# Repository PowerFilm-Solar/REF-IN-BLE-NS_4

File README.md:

# Thank you for your interest in PowerFilm's solar powered BLE reference Designs! Navigate to the Wiki tab to get started: https://github.com/PowerFilm-Solar/REF-IN-BLE-NS_4/wiki

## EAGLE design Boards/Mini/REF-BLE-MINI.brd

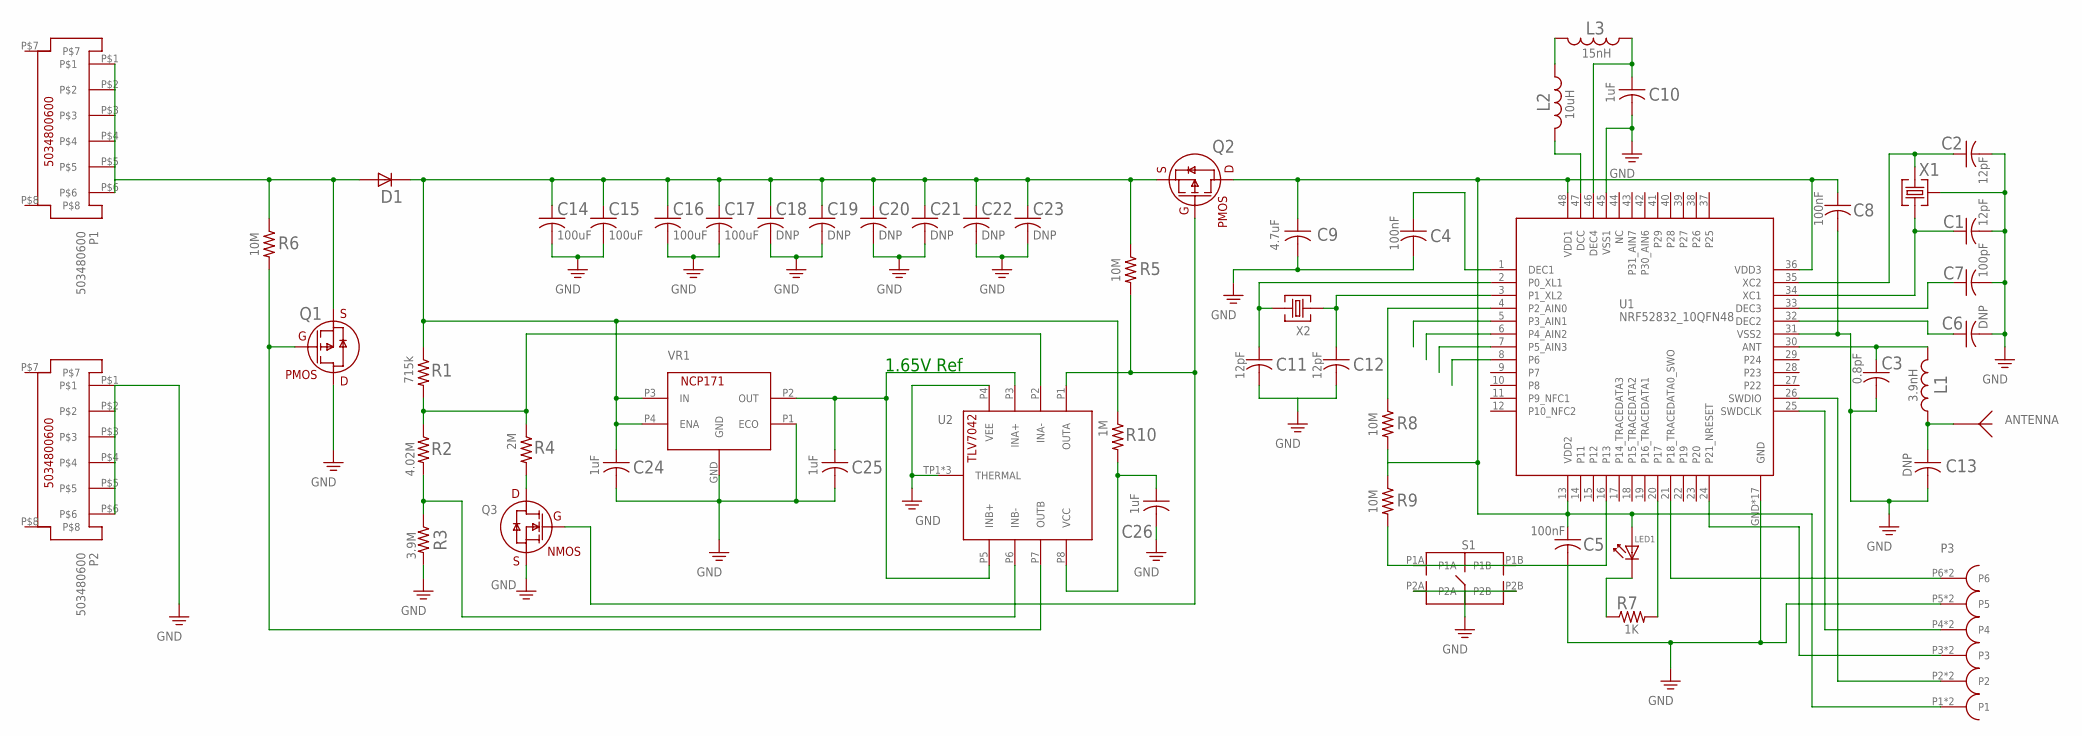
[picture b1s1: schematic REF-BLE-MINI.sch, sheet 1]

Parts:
ANTENNA: BLE-ANTENNA-NORDIC-2
C1, C2, C11, C12: 12pF; C0603
C3: 0.8pF; C0603
C4, C5, C8: 100nF; C0603
C6, C13: DNP; C0603
C7: 100pF; C0603
C9: 4.7uF; C0603
C10, C24, C25, C26: 1uF; C0603
C14, C15, C16, C17: 100uF; C1206
C18, C19, C20, C21, C22, C23: DNP; C1206
D1: BAT43WS-E3-08; SOD-323-VISHAY
L1: 3.9nH; L0603
L2: 10uH; L0603
L3: 15nH; L0603
LED1: LTST-20KGKT; TST-20KGKT
P1, P2: 503480600; 5034800600
P3: EC-06-CTX
Q1, Q2: DMG2305U-13; SOT-23-3-DIODESINC
Q3: NX138AKR; SOT-23-3-RENESAS
R1: 715k; R0603
R2: 4.02M; R0603
R3: 3.9M; R0603
R4: 2M; R0603
R5, R6, R8, R9: 10M; R0603
R7: 1K; R0603
R10: 1M; R0603
S1: EVQ-P7A01P
U1: NRF52832_10QFN48; NRF52832_10
U2: TLV7042DSG
VR1: NCP171
X1: FA-128-32MHZMF10Z-AJ5; FA-128-EPSON
X2: FC-135-32.7680KA-AC0

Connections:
GND: C1.2, C2.2, C3.2, C4.2, C5.2, C6.2, C7.2, C8.2, C9.2, C10.2, C11.2, C12.2, C13.2, C14.2, C15.2, C16.2, C17.2, C18.2, C19.2, C20.2, C21.2, C22.2, C23.2, C24.2, C25.2, P2.P$1, P2.P$2, P2.P$3, P2.P$4, P2.P$5, P2.P$6, P3.P5, P3.P11 (P5), Q1.3 (D), Q3.2 (S), R3.2, S1.P2A, S1.P2B, U1.31 (VSS2), U1.45 (VSS1), U1.GND, U1.P$2 (GND), U1.P$3 (GND), U1.P$4 (GND), U1.P$5 (GND), U1.P$6 (GND), U1.P$7 (GND), U1.P$8 (GND), U1.P$9 (GND), U1.P$10 (GND), U1.P$11 (GND), U1.P$12 (GND), U1.P$13 (GND), U1.P$14 (GND), U1.P$15 (GND), U1.P$16 (GND), U1.P$17 (GND), U2.P4 (VEE), U2.TP1 (THERMAL), U2.TP2 (THERMAL), U2.TP3 (THERMAL), VR1.GND, VR1.P1 (ECO), X1.P2 (P3), X1.P4 (P3)
unnamed: L2.2, U1.47 (DCC)
unnamed: L2.1, L3.2
unnamed: C10.1, L3.1, U1.46 (DEC4)
unnamed: C12.1, U1.3 (P1_XL2), X2.P$1 (1)
unnamed: C4.1, U1.1 (DEC1)
unnamed: C2.1, U1.35 (XC2), X1.P1 (2)
unnamed: C1.1, U1.34 (XC1), X1.P3 (1)
unnamed: C3.1, L1.2, U1.30 (ANT)
unnamed: ANTENNA.P$1, ANTENNA.P$2, C13.1, L1.1
unnamed: C7.1, U1.33 (DEC3)
unnamed: C6.1, U1.32 (DEC2)
unnamed: D1.P2, P1.P$1, P1.P$2, P1.P$3, P1.P$4, P1.P$5, P1.P$6, Q1.2 (S), R6.1
unnamed: C11.1, U1.2 (P0_XL1), X2.P$2 (2)
unnamed: C14.1, C15.1, C16.1, C17.1, C18.1, C19.1, C20.1, C21.1, C22.1, C23.1, C24.1, D1.P1, Q2.2 (S), R1.1, R5.1, R10.1, VR1.P3 (IN), VR1.P4 (ENA)
unnamed: R1.2, R2.1, R4.1, U2.P2 (INA-)
unnamed: Q2.1 (G), Q3.1 (G), R5.2, U2.P1 (OUTA)
unnamed: LED1.C, R7.1
unnamed: R2.2, R3.1, U2.P6 (INB-)
unnamed: R7.2, U1.20 (P17)
unnamed: C25.1, U2.P3 (INA+), U2.P5 (INB+), VR1.P2 (OUT)
unnamed: P3.P4, P3.P10 (P4), U1.25 (SWDCLK)
unnamed: P3.P3, P3.P9 (P3), U1.24 (P21_NRESET)
unnamed: Q1.1 (G), R6.2, U2.P7 (OUTB)
unnamed: R9.2, S1.P1A, S1.P1B, U1.16 (P13)
unnamed: P3.P6, P3.P12 (P6), U1.21 (P18_TRACEDATA0_SWO)
unnamed: P3.P2, P3.P8 (P2), U1.26 (SWDIO)
unnamed: R8.1, U1.4 (P2_AIN0)
unnamed: C5.1, C8.1, C9.1, LED1.A, P3.P1, P3.P7 (P1), Q2.3 (D), R8.2, R9.1, U1.13 (VDD2), U1.36 (VDD3), U1.48 (VDD1)
unnamed: Q3.3 (D), R4.2
unnamed: C26.1, R10.2, U2.P8 (VCC)
PE: C26.2

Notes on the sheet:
1.65V Ref

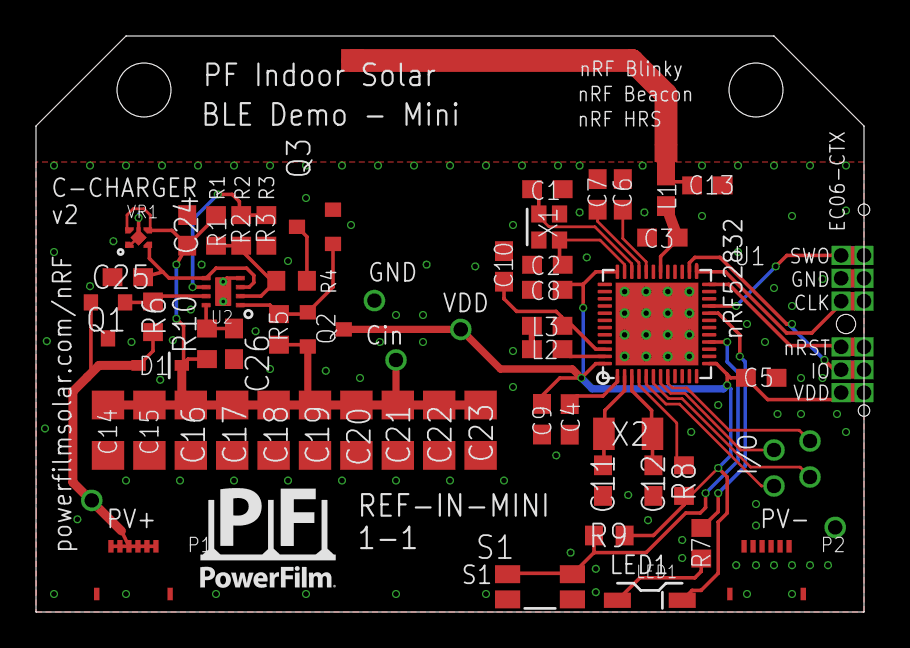
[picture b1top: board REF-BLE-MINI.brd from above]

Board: 2 copper layers, 46.0 x 32.0 mm, 54 parts (0 on the bottom side), 31 nets.

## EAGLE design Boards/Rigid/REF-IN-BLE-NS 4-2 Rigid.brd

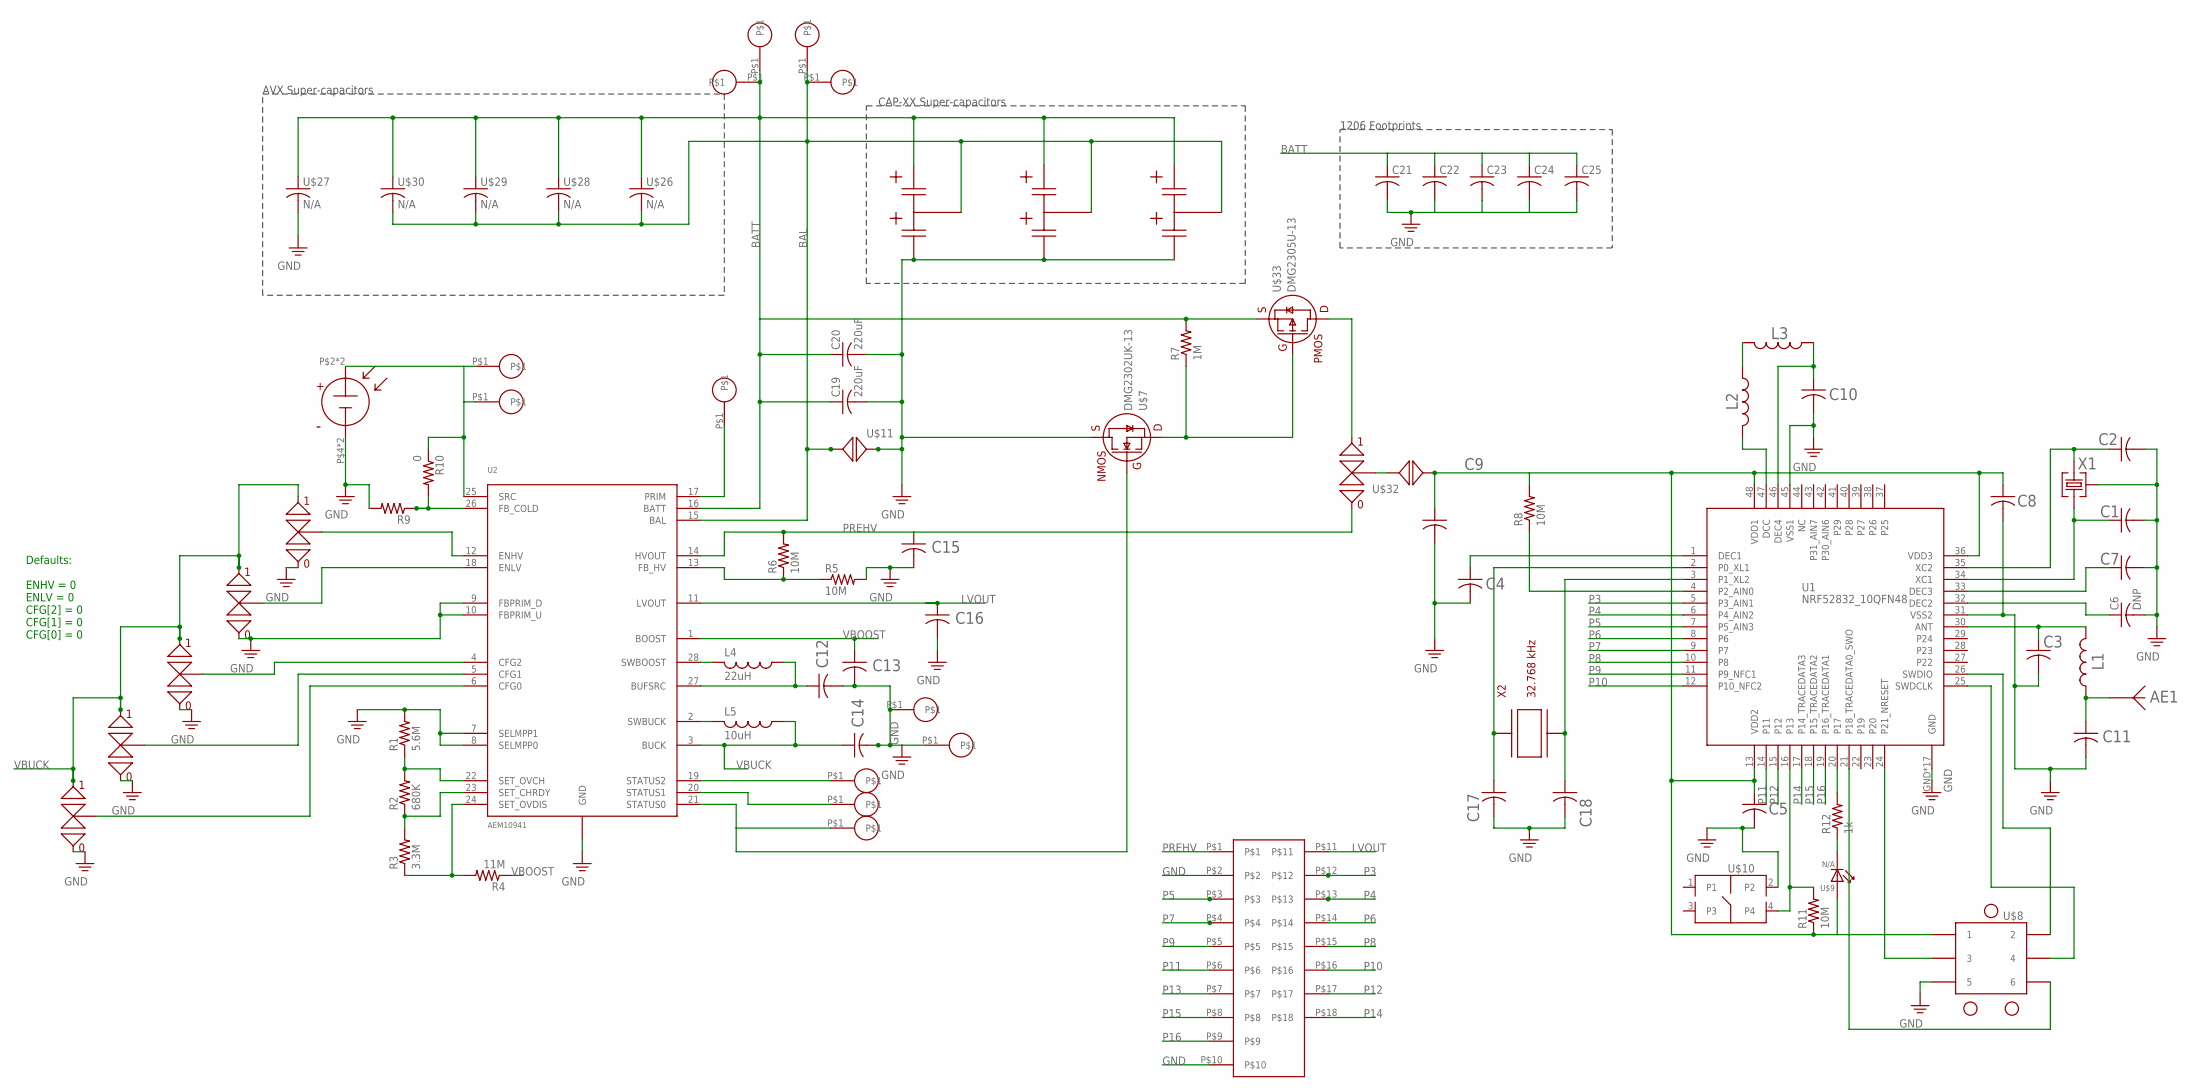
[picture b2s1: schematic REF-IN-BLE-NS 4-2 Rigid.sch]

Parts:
AE1: 2.4GHZ_ANTENNAFLIPPED; BLE_ANTENNA_NORDIC_FLIPPED
C1, C2: 12pF; C0603
C3: 0.8pF; C0603
C4, C5, C8: 100nF; C0603
C6, C11: DNP; C0603
C7: 100pF; C0603
C9: 4.7uF; C0603
C10: 1uF; C0603
C12, C14, C15, C16: 10uF; C0603
C13: 22uF; C0603
C17, C18: 12p; C0603
C19, C20: 220uF; C1206
C21, C22, C23, C24, C25: C-USC1206; C1206
L1: 3.9nH; L0603
L2, L5: 10uH; L0603
L3: 15nH; L0603
L4: 22uH; L1206
R1: 5.6M; R0603
R2: 680K; R0603
R3: 3.3M; R0603
R4: 11M; R0603
R5, R6, R8, R11: 10M; R0603
R7: 1M; R0603
R9: R-US_R0603; R0603
R10: 0; R0603
R12: 1k; R0603
U1: NRF52832_10QFN48; NRF52832_10
U2: AEM10941; QFN28_5X5_05PITCH
U$2, U$3, U$4, U$5, U$6: N/A; DOUBLE_SOLDER_BRIDGE_0_CLOSED
U$7: DMG2302UK-13; SOT-23-3-DIODESINC
U$8: N/A; TC2030-IDC
U$9: N/A; APT1608LZGCK
U$10: MJTP1140; MJTP1140A
U$11, U$32: SOLDER_BRIGDECLOSED; SOLDER_BRIDGE_CLOSED
U$12, U$13, U$14, U$15, U$17, U$18, U$19, U$35, U$36, U$39, U$40, U$41: N/A; 1MM_PAD
U$16: SOLAR_CELL_LL200-2.4-37; SOLAR_CELL_37X54MM
U$20: 18PIN_CONN; 20PIN_CONN
U$23: N/A; CAP-XX_A-TYPE
U$24: N/A; CAP-XX_S-TYPE
U$25: N/A; CAP-XX_W-TYPE
U$26: N/A; BZ01_L-TYPE
U$27: N/A; BZ059_N-TYPE
U$28: N/A; BZ01_S-TYPE
U$29: N/A; BZ05_S-TYPE
U$30: N/A; BZ09_S-TYPE
U$31: DOUBLE_SOLDER_BRIDGE1_CLOSED; DOUBLE_SOLDER_BRIDGE_1_CLOSED
U$33: DMG2305U-13; SOT-23-3-DIODESINC
X1: 32 MHz; FA-128-EPSON
X2: 32.768 kHz; FC-135

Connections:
BAL: U2.15 (BAL), U$11.P$1 (P1), U$19.P$1, U$23.P$1 (BAL), U$24.P$1 (BAL), U$25.P$1 (BAL), U$26.P$3 (2), U$26.P$4 (2), U$28.P$3 (2), U$29.P$3 (2), U$30.P$3 (2), U$41.P$1
BATT: C19.1, C20.1, C21.1, C22.1, C23.1, C24.1, C25.1, R7.2, U2.16 (BATT), U$18.P$1, U$23.P$2 (+), U$24.P$2 (+), U$25.P$2 (+), U$26.P$1 (1), U$26.P$2 (1), U$27.P$1 (1), U$28.P$1 (1), U$28.P$2 (1), U$29.P$1 (1), U$29.P$2 (1), U$30.P$1 (1), U$30.P$2 (1), U$33.2 (S), U$40.P$1
GND: C1.2, C2.2, C3.2, C4.2, C5.2, C6.2, C7.2, C8.2, C9.2, C10.2, C11.2, C12.2, C13.2, C14.2, C15.2, C16.2, C17.2, C18.2, C19.2, C20.2, C21.2, C22.2, C23.2, C24.2, C25.2, R1.2, R5.2, R9.2, U1.31 (VSS2), U1.45 (VSS1), U1.GND, U1.P$2 (GND), U1.P$3 (GND), U1.P$4 (GND), U1.P$5 (GND), U1.P$6 (GND), U1.P$7 (GND), U1.P$8 (GND), U1.P$9 (GND), U1.P$10 (GND), U1.P$11 (GND), U1.P$12 (GND), U1.P$13 (GND), U1.P$14 (GND), U1.P$15 (GND), U1.P$16 (GND), U1.P$17 (GND), U2.7 (SELMPP1), U2.8 (SELMPP0), U2.9 (FBPRIM_D), U2.10 (FBPRIM_U), U2.GND, U2.GND1 (GND), U2.GND2 (GND), U2.GND3 (GND), U2.GND4 (GND), U2.GND5 (GND), U$2.IN0, U$3.IN0, U$4.IN0, U$5.IN0, U$6.IN0, U$7.2 (S), U$8.P5 (5), U$10.2, U$11.P$2 (P2), U$16.P$4 (GND), U$16.P$5 (GND), U$17.P$1, U$20.P$2, U$20.P$10, U$23.P$3 (-), U$24.P$3 (-), U$25.P$3 (-), U$27.P$2 (2), U$35.P$1, X1.P2 (P3), X1.P4 (P3)
HVOUT: C5.1, C8.1, C9.1, R8.2, R11.1, U1.13 (VDD2), U1.36 (VDD3), U1.48 (VDD1), U$8.P1 (1), U$9.A, U$32.P$1 (P1)
LVOUT: C16.1, U2.11 (LVOUT), U$20.P$11
unnamed: L2.2, U1.47 (DCC)
unnamed: L2.1, L3.2
unnamed: C10.1, L3.1, U1.46 (DEC4)
unnamed: C4.1, U1.1 (DEC1)
unnamed: C2.1, U1.35 (XC2), X1.P1 (2)
unnamed: C1.1, U1.34 (XC1), X1.P3 (1)
unnamed: C3.1, L1.2, U1.30 (ANT)
unnamed: AE1.P$1, C11.1, L1.1
unnamed: C7.1, U1.33 (DEC3)
unnamed: C6.1, U1.32 (DEC2)
unnamed: L4.P$2 (2), U2.28 (SWBOOST)
unnamed: C12.1, L4.P$1 (1), U2.27 (BUFSRC)
unnamed: R1.1, R2.2, U2.22 (SET_OVCH)
unnamed: L5.2, U2.2 (SWBUCK)
unnamed: R2.1, R3.2, U2.23 (SET_CHRDY)
unnamed: R11.2, U1.16 (P13), U$10.4
unnamed: R3.1, R4.2, U2.24 (SET_OVDIS)
unnamed: U2.4 (CFG2), U$4.OUT
unnamed: U2.18 (ENLV), U$3.OUT
unnamed: U1.25 (SWDCLK), U$8.P4 (4)
unnamed: U1.24 (P21_NRESET), U$8.P3 (3)
unnamed: U2.12 (ENHV), U$2.OUT
unnamed: U1.26 (SWDIO), U$8.P2 (2)
unnamed: U1.21 (P18_TRACEDATA0_SWO), U$8.P6 (6)
unnamed: U2.5 (CFG1), U$5.OUT
unnamed: U2.6 (CFG0), U$6.OUT
unnamed: R5.1, R6.1, U2.13 (FB_HV)
unnamed: R10.1, U2.25 (SRC), U$16.P$2 (VOUT), U$16.P$3 (VOUT), U$36.P$1, U$39.P$1
unnamed: R12.1, U$9.C
unnamed: R12.2, U1.20 (P17)
unnamed: R9.1, R10.2, U2.26 (FB_COLD)
unnamed: C17.1, U1.2 (P0_XL1), X2.P$1
unnamed: C18.1, U1.3 (P1_XL2), X2.P$2
unnamed: R8.1, U1.4 (P2_AIN0)
unnamed: U$31.OUT, U$32.P$2 (P2)
unnamed: U$31.IN1, U$33.3 (D)
unnamed: R7.1, U$7.3 (D), U$33.1 (G)
P3: U1.5 (P3_AIN1), U$20.P$12
P4: U1.6 (P4_AIN2), U$20.P$13
P5: U1.7 (P5_AIN3), U$20.P$3
P6: U1.8 (P6), U$20.P$14
P7: U1.9 (P7), U$20.P$4
P8: U1.10 (P8), U$20.P$15
P9: U1.11 (P9_NFC1), U$20.P$5
P10: U1.12 (P10_NFC2), U$20.P$16
P11: U1.14 (P11), U$20.P$6
P12: U1.15 (P12), U$20.P$17
P13: U$20.P$7
P14: U1.17 (P14_TRACEDATA3), U$20.P$18
P15: U1.18 (P15_TRACEDATA2), U$20.P$8
P16: U1.19 (P16_TRACEDATA1), U$20.P$9
PREHV: C15.1, R6.2, U2.14 (HVOUT), U$20.P$1, U$31.IN0
PRIM: U2.17 (PRIM), U$12.P$1
STATUS0: U2.21 (STATUS0), U$7.1 (G), U$15.P$1
STATUS1: U2.20 (STATUS1), U$14.P$1
STATUS2: U2.19 (STATUS2), U$13.P$1
VBOOST: C13.1, R4.1, U2.1 (BOOST)
VBUCK: C14.1, L5.1, U2.3 (BUCK), U$2.IN1, U$3.IN1, U$4.IN1, U$5.IN1, U$6.IN1

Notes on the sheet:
Defaults: ENHV = 0 ENLV = 0 CFG[2] = 0 CFG[1] = 0 CFG[0] = 0
CAP-XX Super-capacitors
AVX Super-capacitors
1206 Footprints

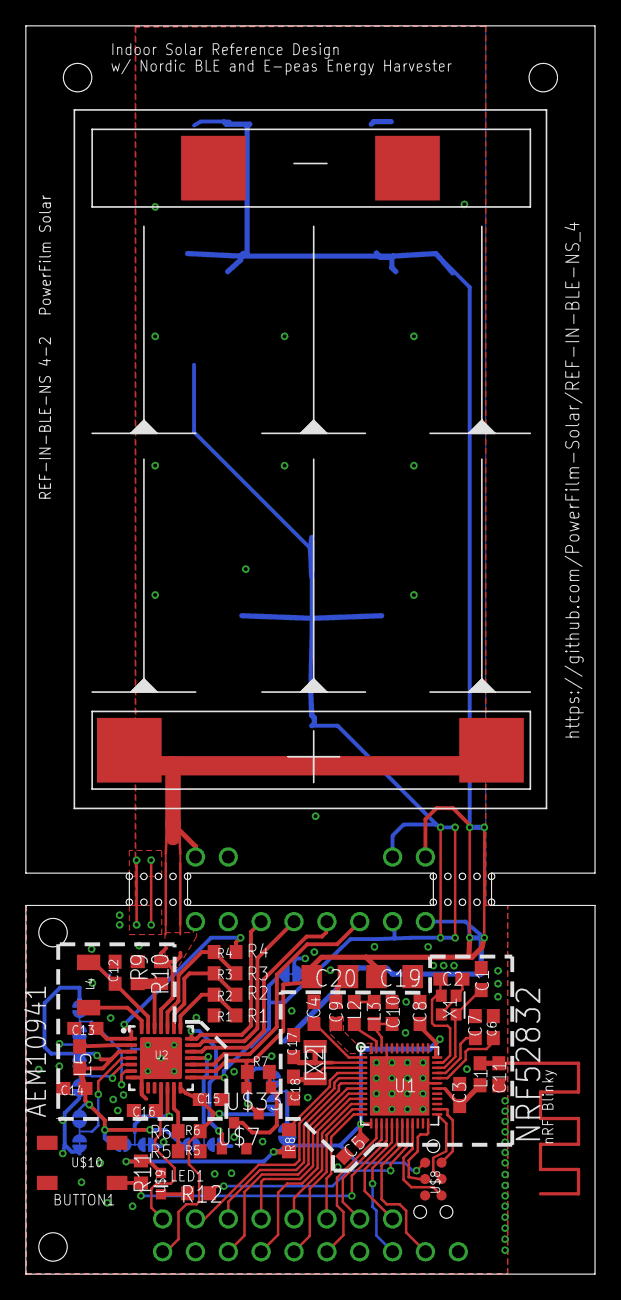
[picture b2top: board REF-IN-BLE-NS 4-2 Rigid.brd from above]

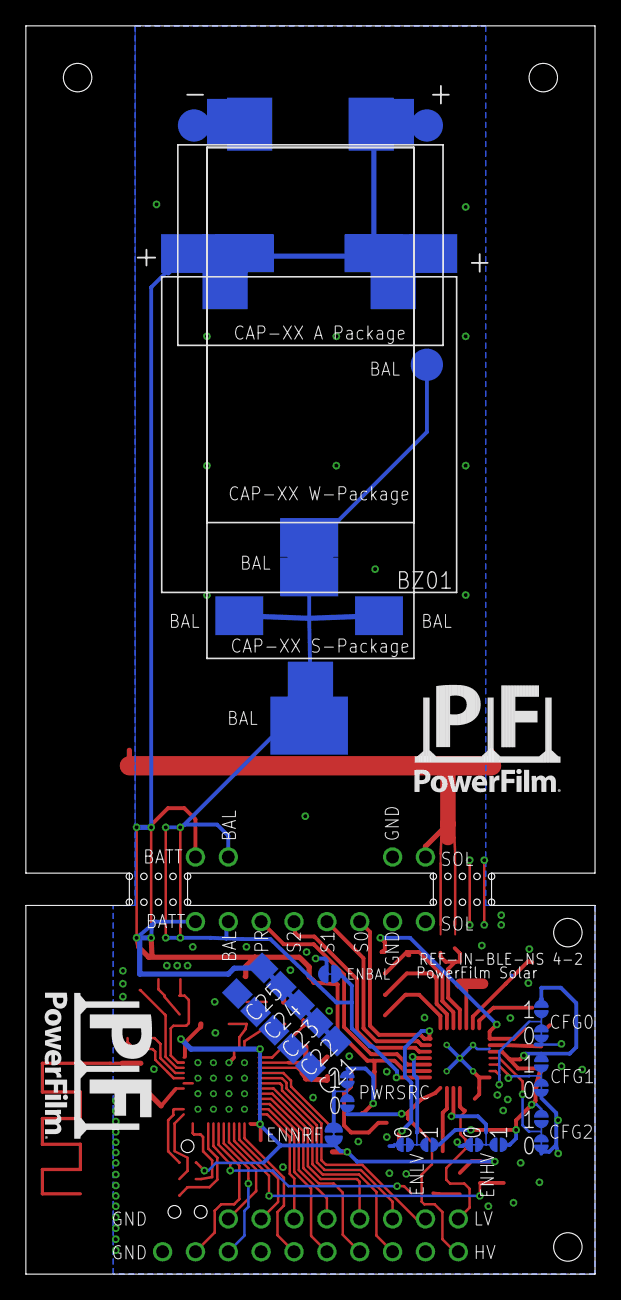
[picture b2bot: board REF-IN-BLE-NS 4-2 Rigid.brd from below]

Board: 4 copper layers, 44.0 x 96.5 mm, 82 parts (21 on the bottom side), 62 nets.

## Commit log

2020-12-02 Added REF-IN-BLE-NS 4-0.lbr, updated brd and sch
2020-12-07 Added caps and prettied up
    Documentation is still needed, will add that as an issue
2020-12-07 Fixed README.md
2020-12-09 Fixed grounding and added labels
2020-12-10 Modified top cream
2020-12-10 Added MPNs to Device Technologies
2020-12-11 Changed MPN for U$1
2021-01-11 Second revision of board Added LDO bypass circuit to attempt to get a higher efficiency from the charge capacitors. Added a way to break away solar from the rest of the assembly. Moved pin connectors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
2021-01-11 Added layout and scematic PDFs for the repo
2021-01-11 Small changes to layout
2021-01-13 Update to v4-1
    Changed filenames to reflect version change
    fixes #1
2021-03-03 v4-1 Final
2021-03-03 Initial Revision 2 Commit
    Added flex board (currently unfinished)
    Added 10M resistor between BATT and VADC
    Rerouted and moved components to have cleaner ground plane near antenna
    Rigid Board:
    Added breakout for many pins on nRF52832
2021-03-03 Converting to multiple folder scheme
2021-03-03 Added pinout for rigid board
2021-04-27 Merged PCBs and examples into one repo
2021-04-27 Deleted old files/folders
2021-04-27 Added photos for wiki
2021-04-27 Added merged hex files
2021-04-27 Added LDO bypass circuit block image
2021-04-27 Added images for bootloader section of wiki
2021-04-27 Added more pictures to bootloader wiki
2021-05-20 Removed internal pullups, changed xtal caps 12pf
2021-06-08 Added photos, modified boards.c
2021-06-08 Added photos to getting started
2021-06-08 More photos for wiki
2021-08-06 Finalized rigid & flex and code
2021-09-01 Create Mini
2021-09-02 Added Mini board files
2021-09-03 renamed layout and schematic files
